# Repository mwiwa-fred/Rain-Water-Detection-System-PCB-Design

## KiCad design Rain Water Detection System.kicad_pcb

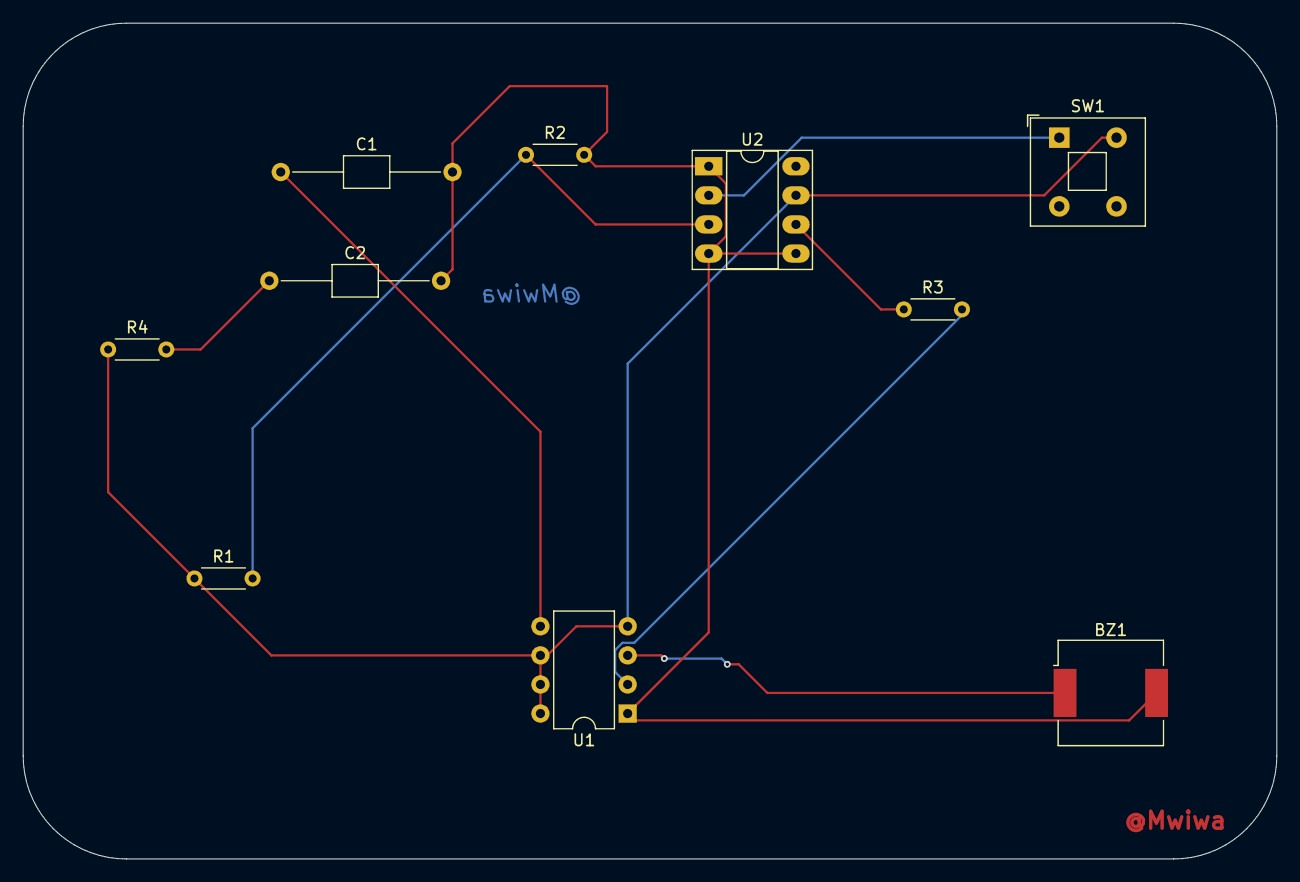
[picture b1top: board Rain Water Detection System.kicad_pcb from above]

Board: 2 copper layers, 109.5 x 73.0 mm, 10 parts (0 on the bottom side), 9 nets.

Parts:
BZ1: Buzzer; Buzzer_CUI_CPT-9019S-SMT
C1, C2: C; C_Axial_L3.8mm_D2.6mm_P15.00mm_Horizontal
R1, R2, R3, R4: R_US; R_Axial_DIN0204_L3.6mm_D1.6mm_P5.08mm_Horizontal
SW1: SW_DPST_x2; SW_Push_2P1T_Toggle_CK_PVA1xxH1xxxxxxV2
U1: ICM7555xP; DIP-8_W7.62mm
U2: LM741; DIP-8_W7.62mm_Socket_LongPads

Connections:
GND: BZ1.2 (-), C1.2, C2.2, R2.2, U1.1 (GND), U2.1 (NULL), U2.4 (V-), U2.5 (NULL)
unnamed: BZ1.1 (+), U1.3 (Q)
unnamed: C2.1, R4.2
unnamed: R3.1, U2.6
unnamed: SW1.1 (A), U2.2 (-)
unnamed: C1.1, U1.5 (CV)
unnamed: R3.2, U1.2 (TR)
unnamed: R1.2, R2.1, U2.3 (+)
VCC: R1.1, R4.1, SW1.2 (B), U1.4 (R), U1.6 (THR), U1.7 (DIS), U1.8 (VCC), U2.7 (V+)
